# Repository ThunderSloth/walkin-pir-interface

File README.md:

# Battery-Powered PIR Motion Interface (Isolated Dry Contact)

## Overview
Battery-powered PIR interface designed to trigger **motion-activated overhead lighting** via an **isolated dry input** on an **XWA11V industrial controller**. Intended for installation in a **walk-in cooler** where running mains power to the sensor is undesirable.

The board detects motion using an **AM312 PIR** and signals the controller by closing a **dry contact (DIN ↔ COM)** through a **PhotoMOS relay**. It also provides a **pass-through connection for an external NTC temperature probe**, allowing temperature sensing to share the same cable run.

All lighting logic and power switching are handled by the controller; this board functions as a low-power, robust peripheral.

---

## Design Summary
- **Power:** 3×AA battery (targeting multi-month to ~1 year life)
- **Isolation:** PhotoMOS relay provides a true dry contact
- **Protection:**
  - Reverse polarity protection on battery input
  - TVS diodes on all field wiring (DIN, COM, NTC probe)
- **Environment:** Cold (~35–40°F), ~6 ft cable runs
- **Assembly:** Hand-solderable THT + simple SMD parts

---

## Design Rationale
- Battery power avoids mains wiring near the sensor
- PhotoMOS isolation prevents ground loops with industrial controls
- TVS protection improves robustness for long, exposed wiring
- Conservative, low-power design prioritizes reliability over complexity

---

## Hardware Documentation

All design, assembly, and fabrication artifacts are published here:

➡️ [WALKIN_PIR_IF Documentation (MkDocs)](https://thundersloth.github.io/walkin-pir-interface/)

---

## Hardware Status

**Rev B sent to fabrication ✅**  
Simplified prototype validated (video below).

- **Rev A:** PIR output sags under direct PhotoMOS LED drive → unreliable switching.
- **Rev B:** Added NPN low-side driver + LED current-limit resistor to isolate PIR output from load.

[https://github.com/user-attachments/assets/d97296ae-1a20-4d2e-b4a4-3fdf33289da8](https://github.com/user-attachments/assets/c07f9941-2b6e-4c99-ae80-a9b624c08050)

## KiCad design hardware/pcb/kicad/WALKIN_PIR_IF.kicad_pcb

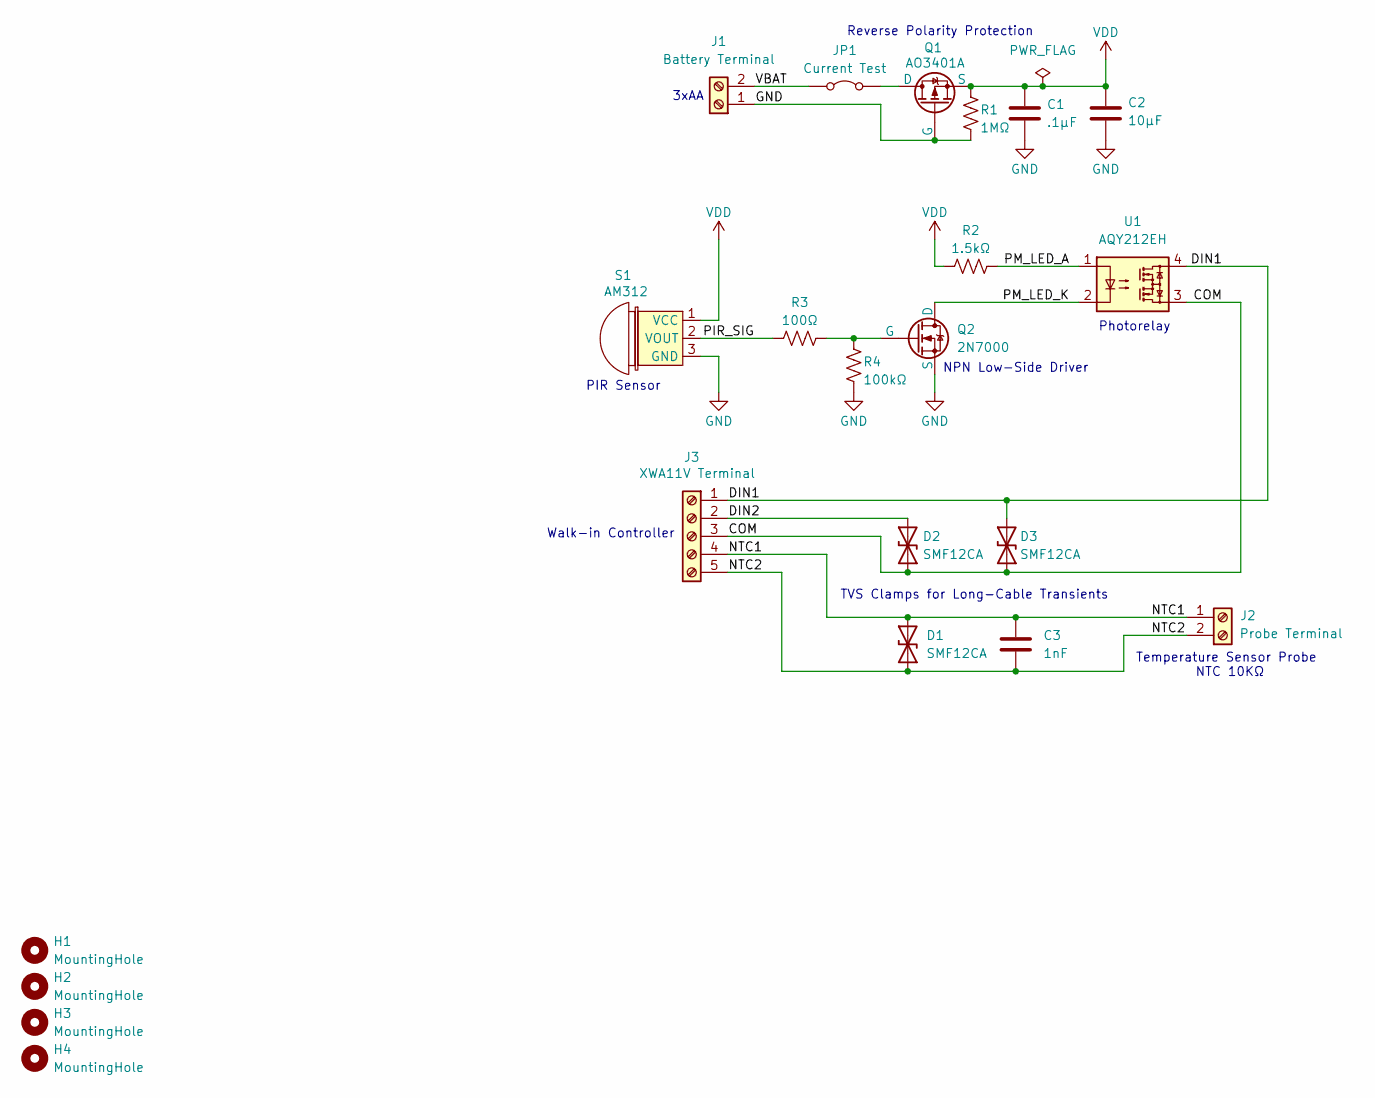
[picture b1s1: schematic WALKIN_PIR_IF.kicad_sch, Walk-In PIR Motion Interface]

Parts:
C1: .1µF; C_Disc_D4.3mm_W1.9mm_P5.00mm
C2: 10µF; C_Disc_D4.3mm_W1.9mm_P5.00mm
C3: 1nF; C_Disc_D4.3mm_W1.9mm_P5.00mm
D1, D2, D3: SMF12CA; D_SOD-123F
H1, H2, H3, H4: MountingHole; MountingHole_3.2mm_M3
J1: Battery Terminal; TerminalBlock_Phoenix_MPT-0,5-2-2.54_1x02_P2.54mm_Horizontal
J2: Probe Terminal; TerminalBlock_Phoenix_MPT-0,5-2-2.54_1x02_P2.54mm_Horizontal
J3: XWA11V Terminal; TerminalBlock_Phoenix_MPT-0,5-5-2.54_1x05_P2.54mm_Horizontal
JP1: Current Test; TestPoint_2Pads_Pitch2.54mm_Drill0.8mm
Q1: AO3401A; SOT-23-3
Q2: 2N7000; TO-92_Inline
R1: 1MΩ; R_Axial_DIN0207_L6.3mm_D2.5mm_P10.16mm_Horizontal
R2: 1.5kΩ; R_Axial_DIN0207_L6.3mm_D2.5mm_P10.16mm_Horizontal
R3: 100Ω; R_Axial_DIN0207_L6.3mm_D2.5mm_P10.16mm_Horizontal
R4: 100kΩ; R_Axial_DIN0207_L6.3mm_D2.5mm_P10.16mm_Horizontal
S1: AM312; PinHeader_1x03_P2.54mm_Vertical
U1: AQY212EH; DIP-4_W7.62mm

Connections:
/COM: D2.1 (A1), D3.1 (A1), J3.3, U1.3
/DIN1: D3.2 (A2), J3.1, U1.4
/DIN2: D2.2 (A2), J3.2
/NTC1: C3.1, D1.2 (A2), J2.1 (VBAT-), J3.4
/NTC2: C3.2, D1.1 (A1), J2.2 (VBAT+), J3.5
/PIR_SIG: R3.1, S1.2 (VOUT)
/PM_LED_A: R2.2, U1.1
/PM_LED_K: Q2.3 (D), U1.2
/VBAT: J1.2 (VBAT-), JP1.1 (A)
GND: C1.2, C2.2, J1.1 (VBAT+), Q1.1 (G), Q2.1 (S), R1.2, R4.2, S1.3 (GND)
unnamed: JP1.2 (B), Q1.3 (D)
unnamed: Q2.2 (G), R3.2, R4.1
VDD: C1.1, C2.1, Q1.2 (S), R1.1, R2.1, S1.1 (VCC)

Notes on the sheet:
PIR Sensor
TVS Clamps for Long-Cable Transients
Photorelay
3xAA
NTC 10KΩ
Walk-in Controller
Temperature Sensor Probe
NPN Low-Side Driver
Reverse Polarity Protection

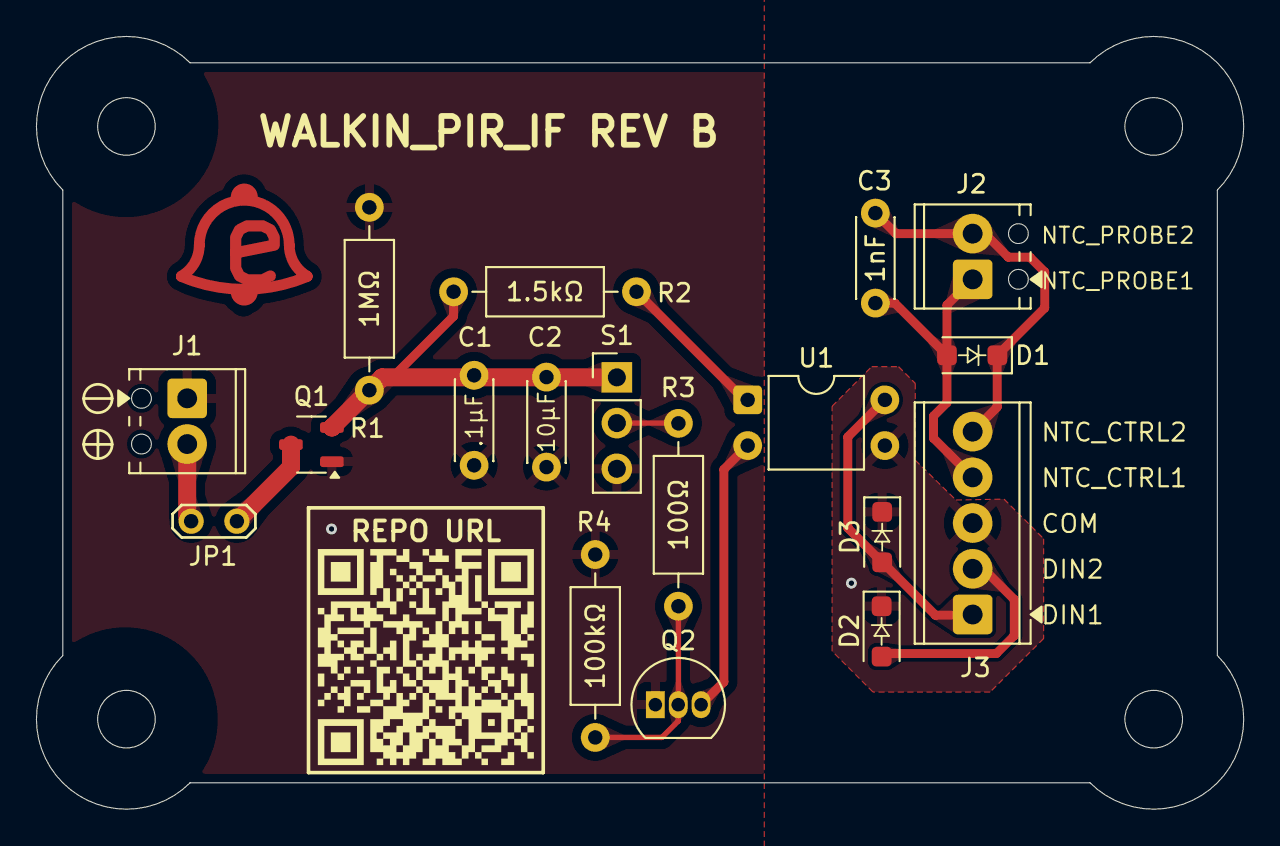
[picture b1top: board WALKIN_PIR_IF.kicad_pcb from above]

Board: 2 copper layers, 67.1 x 42.9 mm, 22 parts (0 on the bottom side), 13 nets.

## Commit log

2025-12-30 Enhance README with project details and design info
    Expanded README with detailed overview, design summary, rationale, and repository contents.
2025-12-31 init
2025-12-31 Add image to README for visual reference
2025-12-31 fab diagram and 3d render
2025-12-31 update 3d render
2025-12-31 Add 3D render image to README
    Added a 3D render image of the PCB to the README.
2025-12-31 Add 3D render image to README
    Added a 3D render image of the WALKIN_PIR_IF PCB to the README.
2026-01-02 Add GitHub Actions workflow for MkDocs deployment
2026-01-02 mkdoc init
2026-01-02 Deployed 4c95ffb with MkDocs version: 1.6.1
2026-01-02 remove old workflow
2026-01-02 2d renders to png on make
2026-01-02 2d renders png instead of svg
2026-01-15 Added npn low side driver for photomos cathode for rev B
2026-01-15 Update hardware status with Rev B details
    Added details about Rev B design and identified issues with Rev A.
2026-01-15 Update hardware status with Rev A and Rev B details
    Clarify Rev A and Rev B findings regarding PIR output.
2026-01-16 update repo link text
2026-01-24 moved pir pulldown r to npn gate and changed value to 100k
2026-01-25 Enhance README with visuals and hardware updates
    Updated README with design summary and hardware status.
